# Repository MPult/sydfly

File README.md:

<!-- PROJECT LOGO -->
<br />
<div align="center">

  <h3 align="center">Sydfly</h3>
  <h4>This is still under Developent</h4> 
  <h4> /syːd/ /flyːr/ </h4>
  <p align="center">
     LEDs for your PAX wardrobe, without the propriatary controller
    <!--<br />
    <a href="https://github.com/mpult/sydfly">View Demo</a>
    ·
    <a href="https://github.com/mpult/sydfly/issues">Report Bug</a>
    ·
    <a href="https://github.com/mpult/sydfly/issues">Request Feature</a>
  </p> -->
</div>

<!-- ABOUT THE PROJECT -->
## About The Project

<!-- [![Product Name Screen Shot][product-screenshot]](https://example.com) -->

I wanted to buy some LEDs, that turn off once I close the door, for my PAX wardrobe. Yet, the price tag convinced me to spend thousands in learning PCB design and creating my own. (No I'm not OK) 

Here's why you should use this:
* You value open-source over time efficiency
* You're a cheapskate
* You hate spending money on a product that actually fully works, so instead you make it yourself.

<p align="right">(<a href="#readme-top">back to top</a>)</p>

<!-- GETTING STARTED -->
## Getting Started

Setting this up varies depending on how legit you want to make it: Own PCB? Or just on a breadboard?
### Parts list

Below is a list of parts required, each have their datasheet in the ``Datasheets`` folder. The links shown are for ``conrad.de``, I am not affiliated with them in any way.

| Count | Part No.                | Part Name                                                                                                                                       |
| ----- | ----------------------- | ----------------------------------------------------------------------------------------------------------------------------------------------- |
| 1     | A000005                 | [Arduino Nano](https://www.conrad.de/de/p/arduino-board-nano-core-nano-atmega328-1172623.html)                                                  |
| 4     | DG350-3.5-03P-14-00AH-1 | [Degson Screw Terminal](https://www.conrad.de/de/p/degson-dg350-3-5-03p-14-00ah-1-schraubklemmblock-2-mm-polzahl-num-3-gruen-1-st-1327185.html) |
| 3     | IRLB8721PBF             | [N-Channel MOSFET](https://www.conrad.de/de/p/infineon-technologies-irlb8721pbf-mosfet-1-n-kanal-65-w-to-220ab-161166.html)                     |
### Breadboard

1. Flash the code from ``Arduino-Code`` on to the Arduino [Instructions](https://support.arduino.cc/hc/en-us/articles/4733418441116-Upload-a-sketch-in-Arduino-IDE)
2. Build the breadboard following the [schematics](./Own-Schematics/Schematics.pdf), proper breadboard diagrams will follow soon (feel free to contribute!)
3. Enjoy the project!

**Optional Steps:**
1. 3D-Print the case from the ``CAD`` folder
2. Add a 45° diffuser for the stylish look

<p align="right">(<a href="#readme-top">back to top</a>)</p>

### PCB Route

Okay so you're hardcore and want to make your own PCB.

You can either use the Gerber files from the release, or make your own. Instructions to make the gerber files will follow soon™

1. Upload the **zipped** Gerber files from the release.
2. Select the options you want, only really important is 2 layered PCB. Rest is all preference
3. Order and wait.
4. Solder the components to the board following the [board Diagram](./Own-Schematics/Board.pdf)
5. Flash the code from ``Arduino-Code`` on to the Arduino [Instructions](https://support.arduino.cc/hc/en-us/articles/4733418441116-Upload-a-sketch-in-Arduino-IDE)
6. Done!

**Optional Steps:**
1. 3D-Print the case from the ``CAD`` folder
2. Add a 45° diffuser for the stylish look

<p align="right">(<a href="#readme-top">back to top</a>)</p>

<!-- ROADMAP -->
## Roadmap

- [x] New README
- [x] Create Release
- [ ] Add multithreading
- [x] Add images to docs.

See the [open issues](https://github.com/mpult/sydfly/issues) for a full list of proposed features (and known issues).

<p align="right">(<a href="#readme-top">back to top</a>)</p>

<!-- CONTRIBUTING -->
## Contributing

Contributions are what make the open source community such an amazing place to learn, inspire, and create. Any contributions you make are **greatly appreciated**.

If you have a suggestion that would make this better, please fork the repo and create a pull request. You can also simply open an issue with the tag "enhancement".
Don't forget to give the project a star! Thanks again!

1. Fork the Project
2. Create your Feature Branch (`git checkout -b feature/AmazingFeature`)
3. Commit your Changes (`git commit -m 'Add some AmazingFeature'`)
4. Push to the Branch (`git push origin feature/AmazingFeature`)
5. Open a Pull Request

<p align="right">(<a href="#readme-top">back to top</a>)</p>

<!-- LICENSE -->
## License

Distributed under the MIT License. See `LICENSE` for more information.

<p align="right">(<a href="#readme-top">back to top</a>)</p>

<!-- ACKNOWLEDGMENTS -->
## Acknowledgments

* [Choose an Open Source License](https://choosealicense.com)
* [Img Shields](https://shields.io)
* [Markdown Template](https://github.com/othneildrew/Best-README-Template)
* [PCBway](https://pcbway.com)

# PCBway Review.

PCBway is the sponsor for this project!

**Disclaimer: I received the SYDFLY PCB prototype from PCBWay for free in exchange for writing this review.**

When it comes to open-source PCB projects, the quality of the prototypes can make a significant difference in the overall success of your project. I recently had the opportunity to try out PCBWay's services for the SYDFLY project, and I must say I'm quite impressed with the experience.

The continued collaboration with PCBWay has made the delevopment of this project possible. The service is honestly incredible, over multiple orders with them the quality has remained excelent. A coupple weeks after a order arrives a representative will reach out and ensure that everything is perfect.

Packaging:
First impressions matter, and PCBWay started off on the right foot with their packaging. The PCBs were carefully wrapped in bubble wrap and vacuum-sealed, ensuring that they arrived in pristine condition. This level of care in packaging demonstrates a commitment to quality and customer satisfaction.

Quality Assurance:
Upon opening the package, I examined the PCBs closely for defects. I'm pleased to report that there were none to be found. The boards looked immaculate, and the solder mask and silkscreen printing were sharp and well-executed. I also conducted a thorough conductivity and shorts check, and everything passed with flying colors. This attention to detail and quality control is crucial.

Finish Selection:
One important piece of advice I'd like to share is the importance of choosing the right finish for your PCBs. PCBWay offers a variety of finish options, and it's essential to select the one that suits your project. In my experience, the lead-free finish worked perfectly. However, it's worth noting that if you're not familiar with different finishes, seeking guidance is advisable to ensure compatibility with your components.

Shipping Speed and Cost:
I was pleasantly surprised by the efficiency of PCBWay's shipping service. Not only was it faster, but it was also more cost-effective compared to my previous experience with another PCB manufacturer. This is a significant advantage for anyone looking to get their prototypes quickly without breaking the bank.

Overall Impressions:
In conclusion, my experience with PCBWay for the SYDFLY project has been overwhelmingly positive. The quality of the PCBs, the attention to detail, and the reliable shipping service all contribute to an excellent overall experience. It's worth noting that the quality is on par with some of other well-known PCB manufacturers, which speaks volumes about PCBWay's capabilities.

In the interest of full transparency, I did receive these SYDFLY PCB prototypes from PCBWay at no cost in exchange for this review. However, I want to emphasize that my assessment is based solely on the quality of the product and the overall experience.

If you're working on an open-source PCB project like SYDFLY, I highly recommend giving PCBWay a try. Their commitment to quality, fast and affordable shipping, and range of finish options make them a strong contender in the PCB manufacturing space.

<!-- MARKDOWN LINKS & IMAGES -->
<!-- https://www.markdownguide.org/basic-syntax/#reference-style-links -->

[product-screenshot]: images/screenshot.png

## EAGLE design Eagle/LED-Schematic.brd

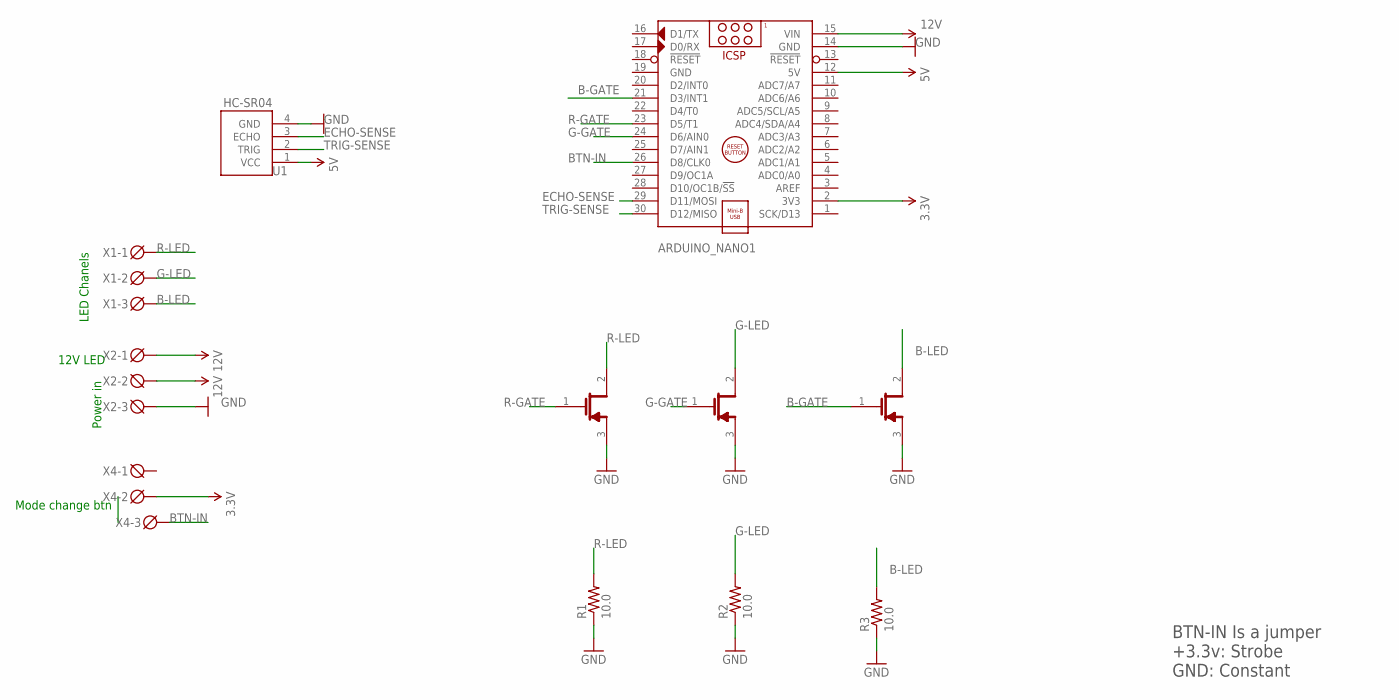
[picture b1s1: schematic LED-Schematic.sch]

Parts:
ARDUINO_NANO1: ARDUINO_NANO
Q1, Q2, Q3: INFINEON_IRLB8721PBFINFINEON_IRLB8721PBF_0_0; INFINEON_IRLB8721PBF_0
R1, R2, R3: 10.0; AXIAL-0.3
U1: HC-SR04; XCVR_HC-SR04
X1, X2, X4: DG3XX-03-3.5; DG350-3.5-03P

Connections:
3.3V: ARDUINO_NANO1.2 (3V3), X4.2
5V: ARDUINO_NANO1.12 (5V), U1.1 (VCC)
12V: ARDUINO_NANO1.15 (VIN), X2.1, X2.2
B-GATE: ARDUINO_NANO1.21 (D3/INT1), Q3.1 (G)
B-LED: Q3.2 (D), R3.P$2 (2), X1.3
BTN-IN: ARDUINO_NANO1.26 (D8/CLK0), X4.3
ECHO-SENSE: ARDUINO_NANO1.29 (D11/MOSI), U1.3 (ECHO)
G-GATE: ARDUINO_NANO1.24 (D6/AIN0), Q2.1 (G)
G-LED: Q2.2 (D), R2.P$2 (2), X1.2
GND: ARDUINO_NANO1.14 (GND), ARDUINO_NANO1.19 (GND), Q1.3 (S), Q2.3 (S), Q3.3 (S), R1.P$1 (1), R2.P$1 (1), R3.P$1 (1), U1.4 (GND), X2.3
R-GATE: ARDUINO_NANO1.23 (D5/T1), Q1.1 (G)
R-LED: Q1.2 (D), R1.P$2 (2), X1.1
TRIG-SENSE: ARDUINO_NANO1.30 (D12/MISO), U1.2 (TRIG)

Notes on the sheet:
Mode change btn
BTN-IN Is a jumper +3.3v: Strobe GND: Constant
Power in
12V LED
LED Chanels

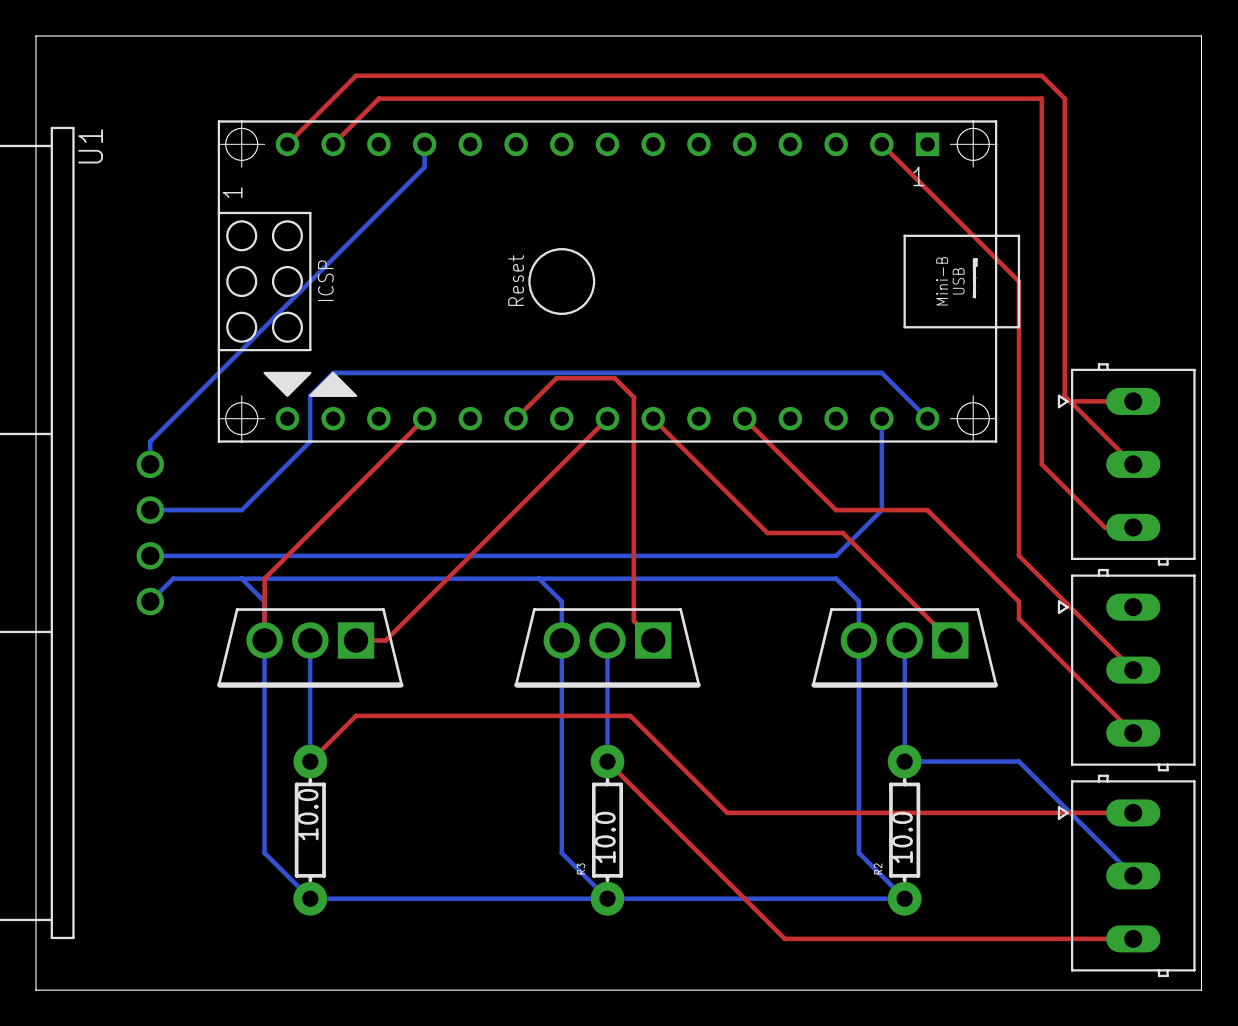
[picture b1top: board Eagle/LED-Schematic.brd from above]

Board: 2 copper layers, 64.8 x 53.0 mm, 11 parts (0 on the bottom side), 13 nets.

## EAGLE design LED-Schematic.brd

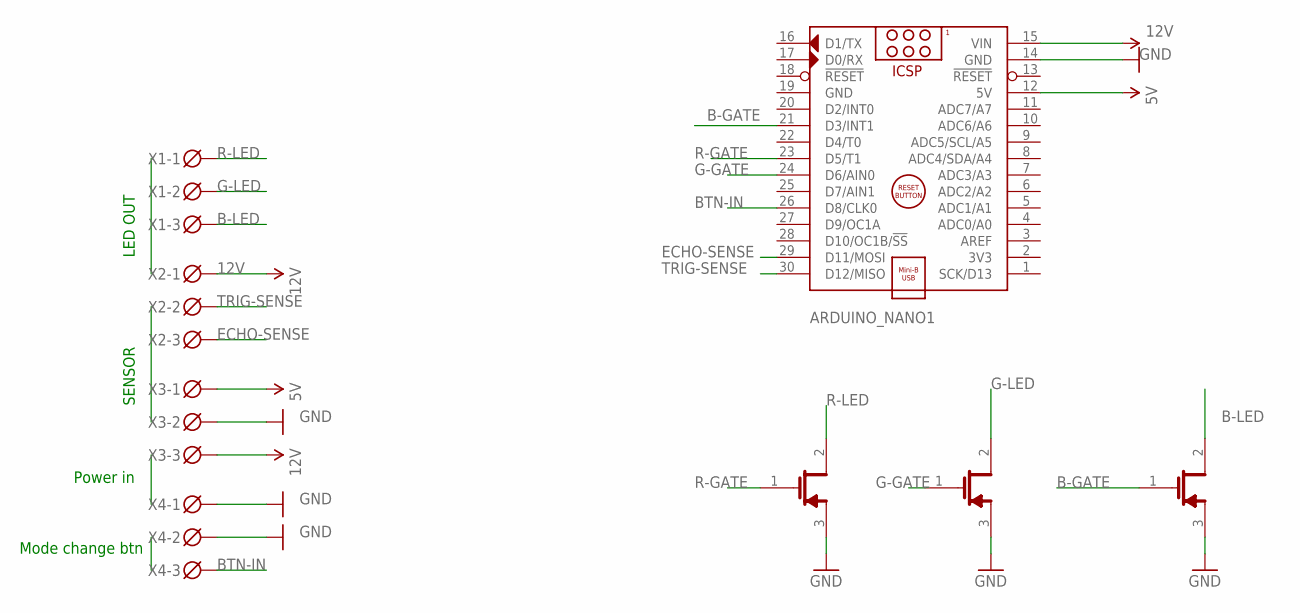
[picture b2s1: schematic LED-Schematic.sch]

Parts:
ARDUINO_NANO1: ARDUINO_NANO
Q1, Q2, Q3: INFINEON_IRLB8721PBFINFINEON_IRLB8721PBF_0_0; INFINEON_IRLB8721PBF_0
X1, X2, X3, X4: DG3XX-03-3.5; DG350-3.5-03P

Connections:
5V: ARDUINO_NANO1.12 (5V), X3.1
12V: ARDUINO_NANO1.15 (VIN), X2.1, X3.3
B-GATE: ARDUINO_NANO1.21 (D3/INT1), Q3.1 (G)
B-LED: Q3.2 (D), X1.3
BTN-IN: ARDUINO_NANO1.26 (D8/CLK0), X4.3
ECHO-SENSE: ARDUINO_NANO1.29 (D11/MOSI), X2.3
G-GATE: ARDUINO_NANO1.24 (D6/AIN0), Q2.1 (G)
G-LED: Q2.2 (D), X1.2
GND: ARDUINO_NANO1.14 (GND), ARDUINO_NANO1.19 (GND), Q1.3 (S), Q2.3 (S), Q3.3 (S), X3.2, X4.1, X4.2
R-GATE: ARDUINO_NANO1.23 (D5/T1), Q1.1 (G)
R-LED: Q1.2 (D), X1.1
TRIG-SENSE: ARDUINO_NANO1.30 (D12/MISO), X2.2

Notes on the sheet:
Power in
Mode change btn
SENSOR
LED OUT

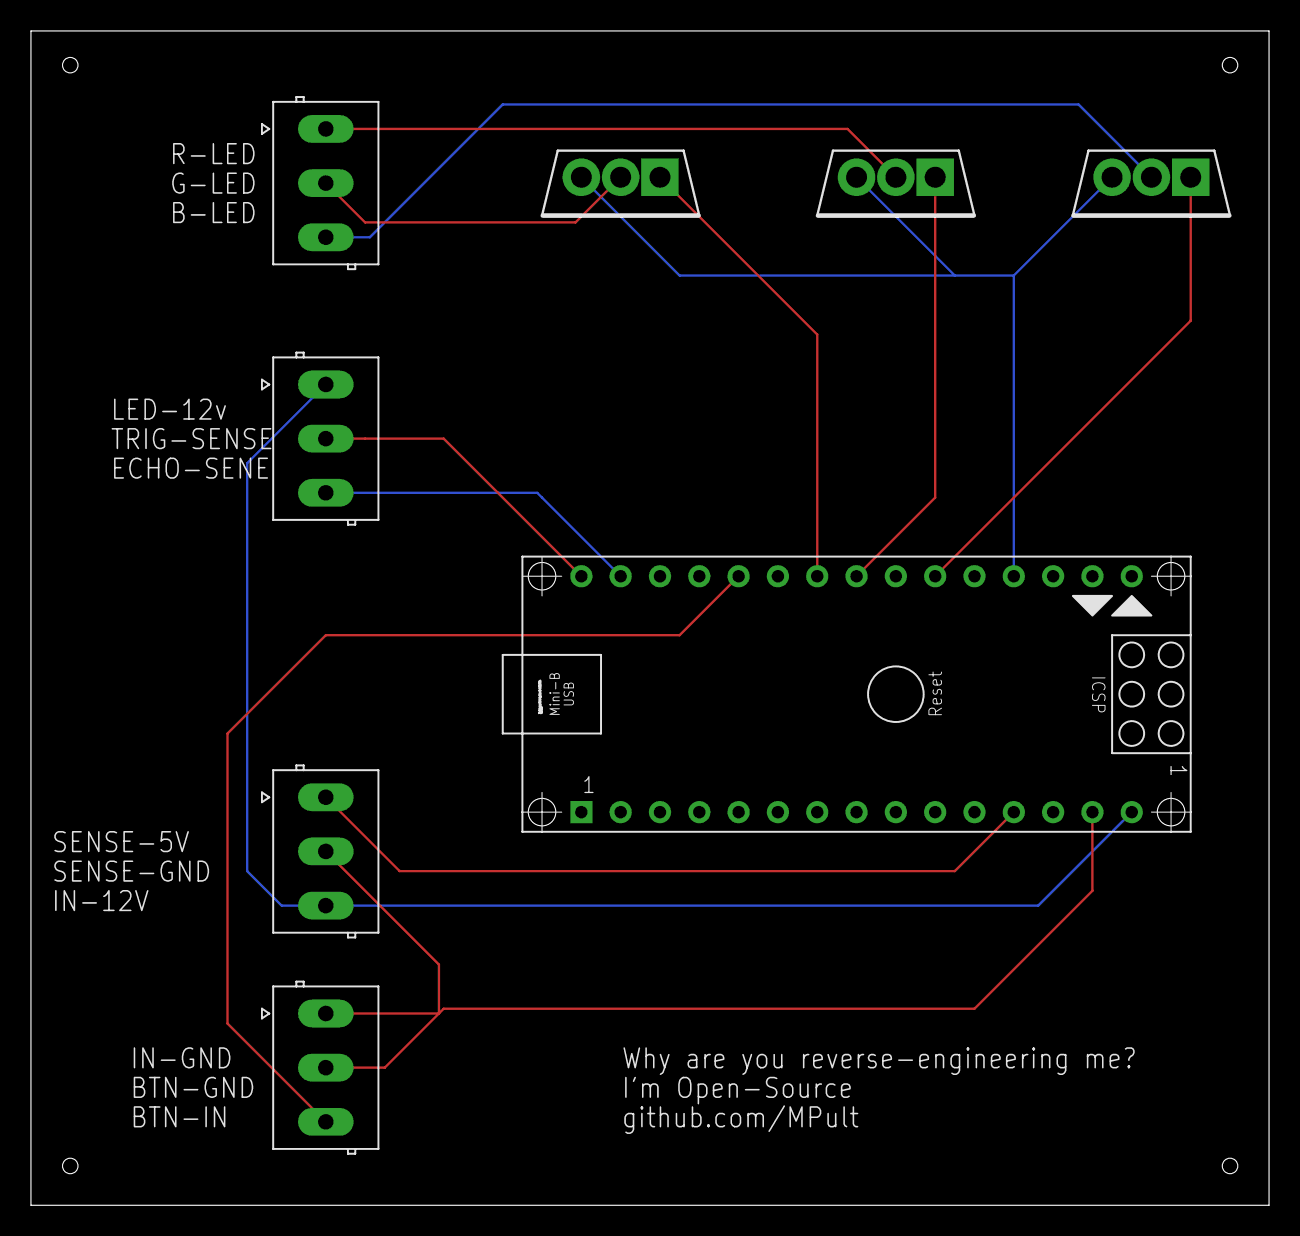
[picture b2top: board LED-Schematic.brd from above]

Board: 2 copper layers, 80.0 x 75.9 mm, 8 parts (0 on the bottom side), 12 nets.

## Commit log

2023-01-15 PCB design
2023-01-16 Added arduino to schematic, added PCB board, added gitignore
2023-01-16 Remove ignored files
2023-01-17 swapped mosfets to infineon IRLs
2023-01-20 Adding Datasheets, replace screw terms
2023-01-20 Before reroute
2023-01-20 addign silk screen labels
2023-01-22 Last Revamp, i promise
2023-01-23 Adding Case 3D Model
2023-01-26 Adding PCB Design export
2023-02-12 Final Edits before production
2023-02-13 Adding Licence
2023-02-13 Revamping DOcs
2023-03-14 Generating new Gerber Files for Production
2023-08-01 Adding images to docs
2023-08-17 Integrated

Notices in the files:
parts and their libraries:
SparkFun-Resistors: Licensing: Creative Commons ShareAlike 4.0 International - https://creativecommons.org/licenses/by-sa/4.0
